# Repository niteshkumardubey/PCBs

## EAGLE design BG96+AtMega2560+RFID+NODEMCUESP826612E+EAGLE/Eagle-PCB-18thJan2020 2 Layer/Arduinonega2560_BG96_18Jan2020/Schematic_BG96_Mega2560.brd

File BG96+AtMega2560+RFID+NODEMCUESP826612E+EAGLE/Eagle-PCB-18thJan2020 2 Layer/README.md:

# Eagle-PCB
All the PCBs are designed in Autodesk Eagle

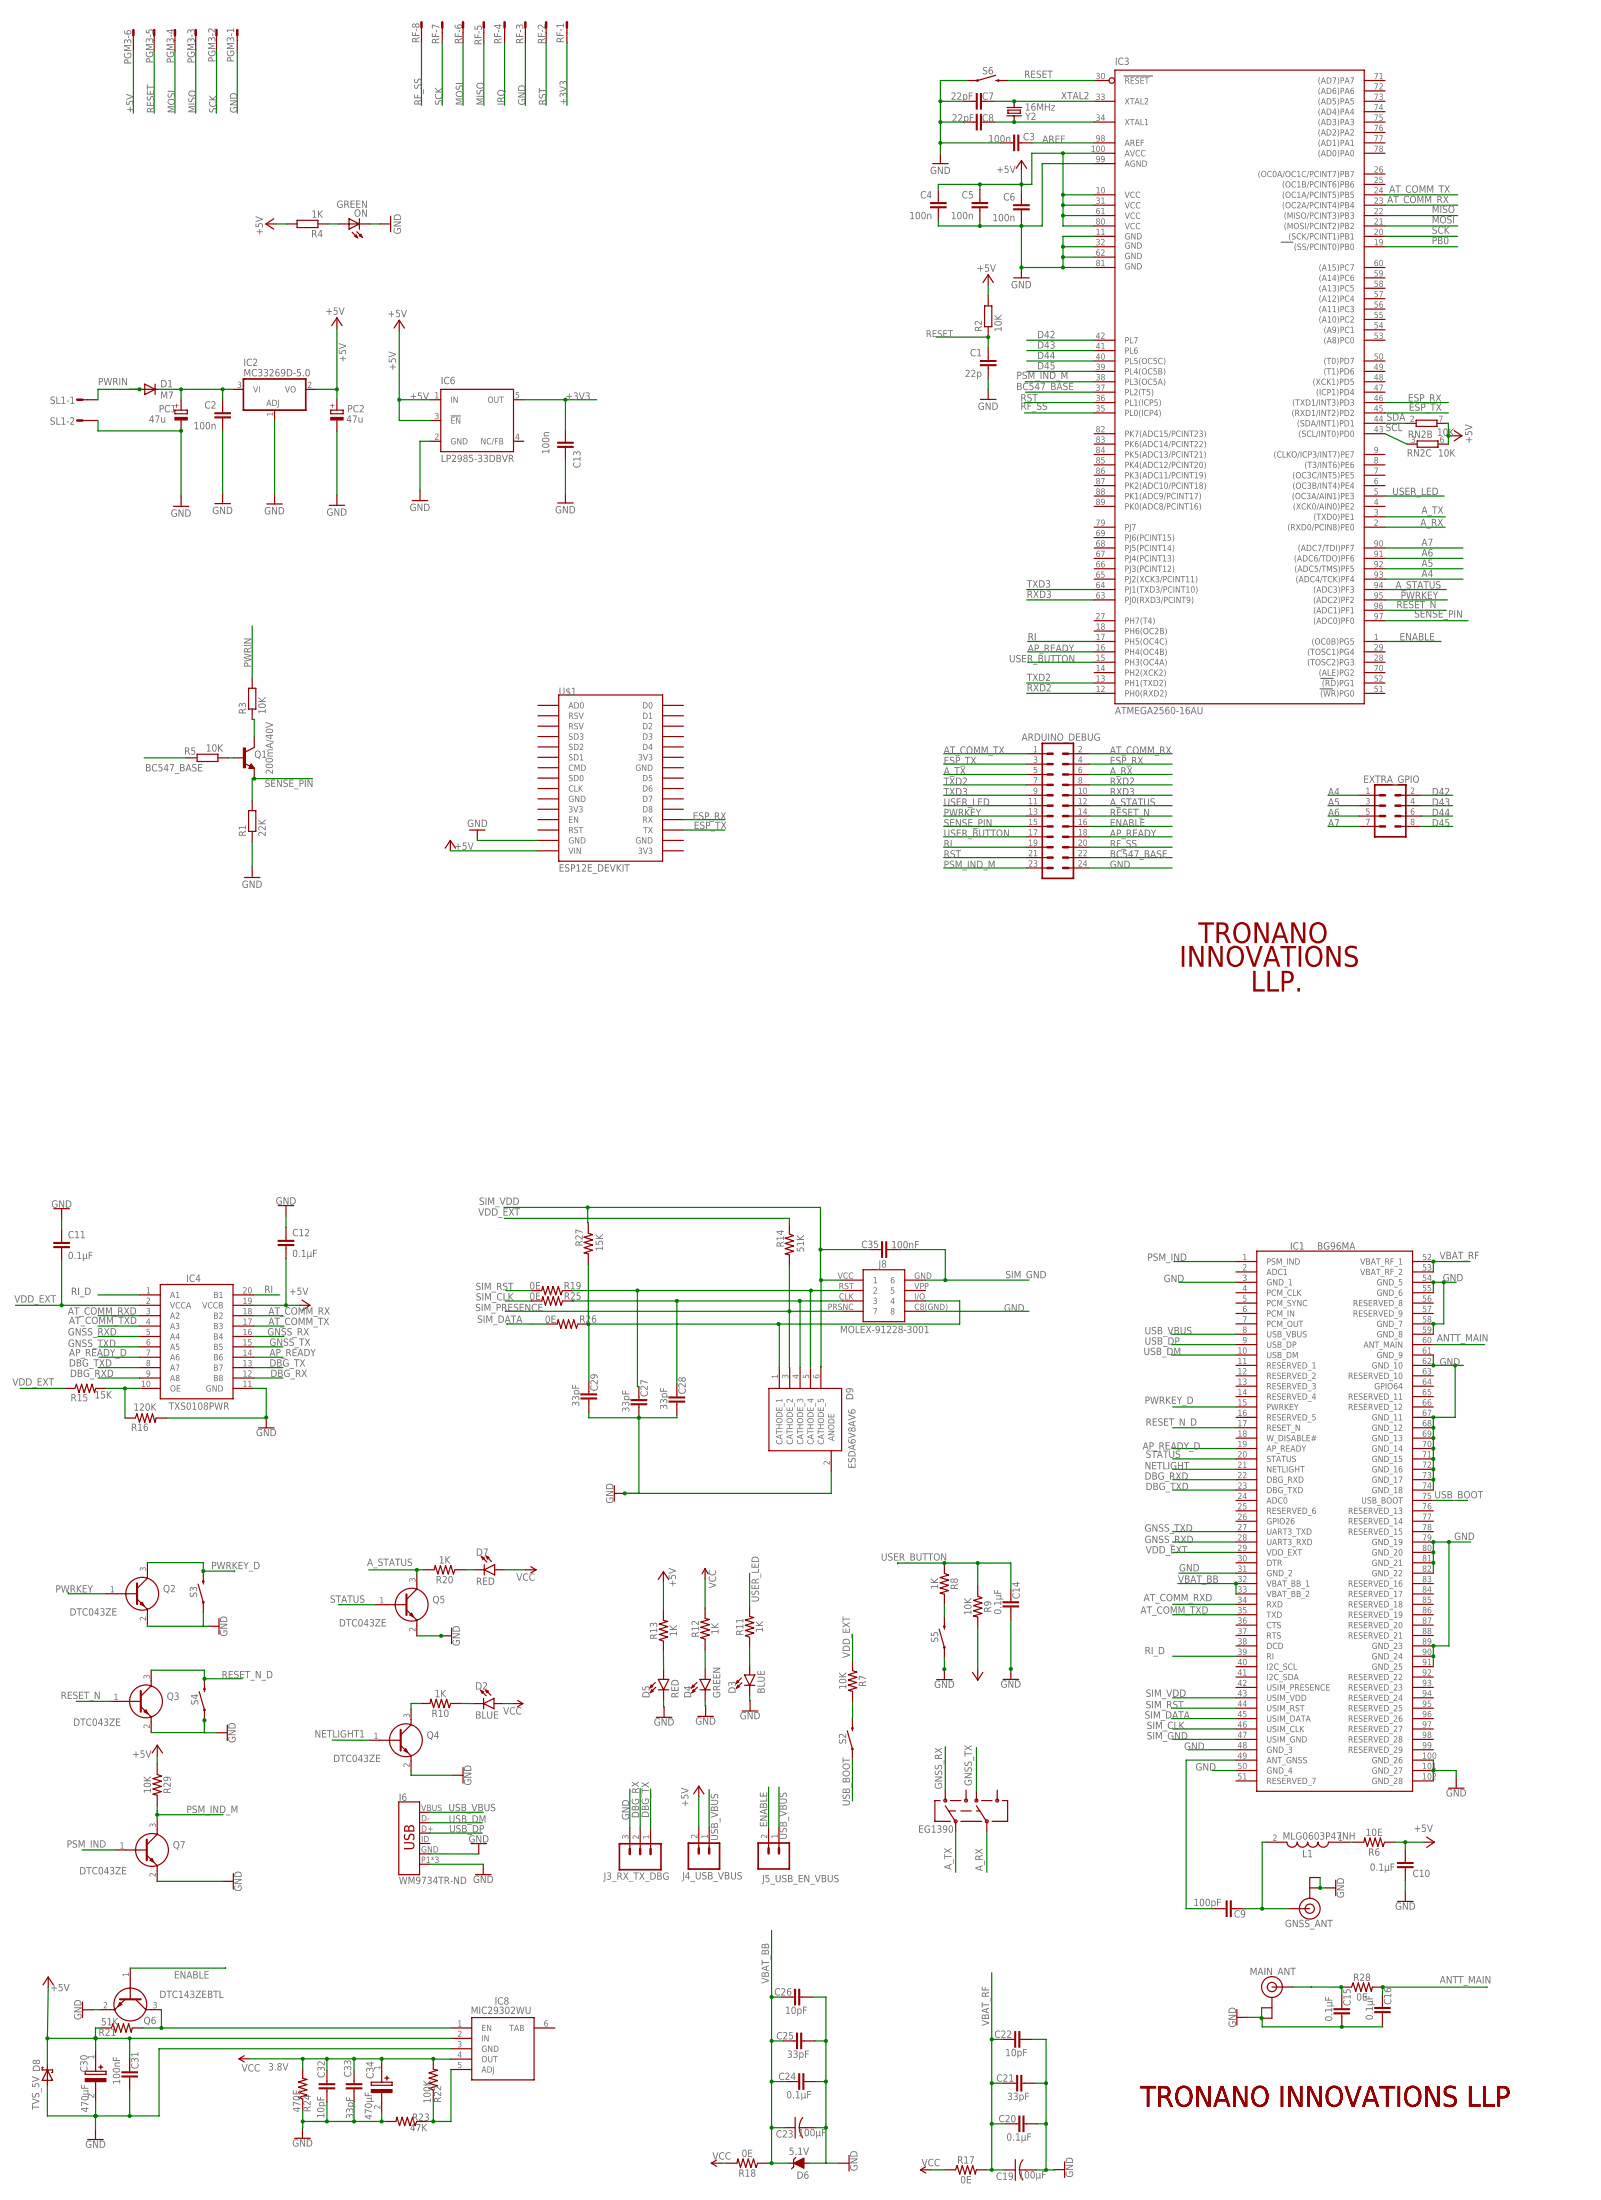
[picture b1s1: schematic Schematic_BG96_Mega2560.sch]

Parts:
ARDUINO_DEBUG: CONN_12X2; 2X12
C1: 22p; C0805
C2, C3, C4, C5, C6, C13: 100n; C0805
C7, C8: 22pF; C0805
C9: 100pF; 0805
C10, C11, C12, C14, C15, C16, C20, C24: 0.1µF; 0805
C19, C23: 100µF; C0805K
C21, C25, C27, C28, C29, C33: 33pF; 0805
C22, C26, C32: 10pF; 0805
C30, C34: 470µF; CAPPM7343X310N
C31, C35: 100nF; 0805
D1: M7; SMB
D2, D3: BLUE; LED-1206
D4: GREEN; LED-1206
D5, D7: RED; LED-1206
D6: 5.1V; SOD-323
D8: TVS_5V; SOD123FL
D9: ESDA6V8AV6; SOTFL50P160X60-6N
EG1390: SWITCH-DPDT-SMD-AYZ0202; SWITCH_DPDT_SMD_AYZ0202
EXTRA_GPIO: CONN_04X2; 2X4
GNSS_ANT: U.FL
IC1: BG96MA
IC2: MC33269D-5.0; DPACK
IC3: ATMEGA2560-16AU; TQFP100
IC4: TXS0108PWR; SOP65P640X120-20N
IC6: LP2985-33DBVR; SOT23-DBV
IC8: MIC29302WU; 6-PIN-TO-263
J3_RX_TX_DBG: CONN_03LOCK; 1X03_LOCK
J4_USB_VBUS, J5_USB_EN_VBUS: CONN_02; 1X02
J6: WM9734TR-ND; USB-B-MICRO-SMD_VERT
J8: MOLEX-91228-3001; MOLEX-912283001
L1: MLG0603P47NH; INDC0603X33N
MAIN_ANT: U.FL
ON: GREEN; CHIPLED_1206
PC1, PC2: 47u; PANASONIC_D
PGM3: S06P
Q1: 200mA/40V; TO-92-EZ
Q2, Q3, Q4, Q5, Q7: DTC043ZE; SOTFL50P160X85-3N
Q6: DTC143ZEBTL; SOTFL50P160X85-3N
R1: 22K; R0805W
R2: 10K; R0805
R3, R5: 10K; R0805W
R4: 1K; R0805
R6: 10E; 0805
R7, R9, R29: 10K; 0805
R8, R10, R11, R12, R13, R20: 1K; 0805
R14, R21: 51K; 0805
R15, R27: 15K; 0805
R16: 120K; 0805
R17, R18, R19, R25, R26, R28: 0E; 0805
R22: 100K; 0805
R23: 47K; 0805
R24: 470E; 0805
RF: S08P
RN2: 10K; CAT16
S2: USB_BOOT_SMD-6.2; TACTILE_SWITCH_SMD_6.2MM_TALL
S3: PWR_KEY_SMD-6.2; TACTILE_SWITCH_SMD_6.2MM_TALL
S4: RST_SMD-6.2; TACTILE_SWITCH_SMD_6.2MM_TALL
S5: USR_SMD-6.2; TACTILE_SWITCH_SMD_6.2MM_TALL
S6: ARD_RST; TACTILE_SWITCH_SMD_6.2MM_TALL
SL1: M02S; 02P
U$1: ESP12E_DEVKIT
Y2: 16MHz; HC49US

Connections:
3.8V: C32.1, C33.1, C34.1 (+), IC8.4 (OUT), R22.2, R24.2
+3V3: C13.2, IC6.5 (OUT), RF.1
+5V: C4.1, C5.1, C6.1, C10.1, C12.2, C30.1 (+), C31.1, D8.C, IC2.2 (VO), IC3.10 (VCC), IC3.31 (VCC1), IC3.61 (VCC2), IC3.80 (VCC3), IC3.100 (AVCC), IC4.19 (VCCB), IC6.1 (IN), IC6.3 (!EN), IC8.2 (IN), J4_USB_VBUS.2, PC2.+, PGM3.6, R2.2, R4.2, R6.1, R9.2, R13.2, R21.1, R29.1, RN2.6 (2), RN2.7 (2), U$1.VIN
A4: EXTRA_GPIO.1, IC3.93 ((ADC4/TCK)PF4)
A5: EXTRA_GPIO.3, IC3.92 ((ADC5/TMS)PF5)
A6: EXTRA_GPIO.5, IC3.91 ((ADC6/TDO)PF6)
A7: EXTRA_GPIO.7, IC3.90 ((ADC7/TDI)PF7)
ANTT_MAIN: C16.1, IC1.60 (ANT_MAIN), R28.2
AP_READY: ARDUINO_DEBUG.18, IC3.16 (PH4(OC4B)), IC4.14 (B6)
AP_READY_D: IC1.19 (AP_READY), IC4.7 (A6)
AREF: C3.1, IC3.98 (AREF)
AT_COMM_RX: ARDUINO_DEBUG.2, IC3.23 ((OC2A/PCINT4)PB4), IC4.18 (B2)
AT_COMM_RXD: IC1.34 (RXD), IC4.3 (A2)
AT_COMM_TX: ARDUINO_DEBUG.1, IC3.24 ((OC1A/PCINT5)PB5), IC4.17 (B3)
AT_COMM_TXD: IC1.35 (TXD), IC4.4 (A3)
A_RX: ARDUINO_DEBUG.6, EG1390.5, IC3.2 ((RXD0/PCIN8)PE0)
A_STATUS: ARDUINO_DEBUG.12, IC3.94 ((ADC3)PF3), Q5.3 (C), R20.2
A_TX: ARDUINO_DEBUG.5, EG1390.2, IC3.3 ((TXD0)PE1)
BC547_BASE: ARDUINO_DEBUG.22, IC3.37 (PL2(T5)), R5.2
D42: EXTRA_GPIO.2, IC3.42 (PL7)
D43: EXTRA_GPIO.4, IC3.41 (PL6)
D44: EXTRA_GPIO.6, IC3.40 (PL5(OC5C))
D45: EXTRA_GPIO.8, IC3.39 (PL4(OC5B))
DBG_RX: IC4.12 (B8), J3_RX_TX_DBG.2
DBG_RXD: IC1.22 (DBG_RXD), IC4.9 (A8)
DBG_TX: IC4.13 (B7), J3_RX_TX_DBG.1
DBG_TXD: IC1.23 (DBG_TXD), IC4.8 (A7)
ENABLE: ARDUINO_DEBUG.16, IC3.1 ((OC0B)PG5), J5_USB_EN_VBUS.2, Q6.1 (B)
ESP_RX: ARDUINO_DEBUG.4, IC3.46 ((TXD1/INT3)PD3), U$1.RX
ESP_TX: ARDUINO_DEBUG.3, IC3.45 ((RXD1/INT2)PD2), U$1.TX
GND: ARDUINO_DEBUG.24, C1.2, C2.2, C3.2, C4.2, C5.2, C6.2, C7.2, C8.2, C10.2, C11.1, C12.1, C13.1, C14.2, C15.2, C16.2, C19.2, C20.2, C21.2, C22.2, C23.2, C24.2, C25.2, C26.2, C27.2, C28.2, C29.2, C30.2 (-), C31.2, C32.2, C33.2, C34.2 (-), D3.C, D4.C, D5.C, D6.A, D8.A, D9.2 (ANODE), GNSS_ANT.1 (GND), GNSS_ANT.2 (GND), IC1.3 (GND_1), IC1.31 (GND_2), IC1.48 (GND_3), IC1.50 (GND_4), IC1.54 (GND_5), IC1.55 (GND_6), IC1.58 (GND_7), IC1.59 (GND_8), IC1.61 (GND_9), IC1.62 (GND_10), IC1.67 (GND_11), IC1.68 (GND_12), IC1.69 (GND_13), IC1.70 (GND_14), IC1.71 (GND_15), IC1.72 (GND_16), IC1.73 (GND_17), IC1.74 (GND_18), IC1.79 (GND_19), IC1.80 (GND_20), IC1.81 (GND_21), IC1.82 (GND_22), IC1.89 (GND_23), IC1.90 (GND_24), IC1.91 (GND_25), IC1.100 (GND_26), IC1.101 (GND_27), IC1.102 (GND_28), IC2.1 (ADJ), IC3.11 (GND), IC3.32 (GND1), IC3.62 (GND2), IC3.81 (GND3), IC3.99 (AGND), IC4.11 (GND), IC6.2 (GND), IC8.3 (GND), J3_RX_TX_DBG.3, J6.GND, J6.P1 (SHIELD), J6.P2 (SHIELD), J6.P3 (SHIELD), J8.C8(GND) (8), MAIN_ANT.1 (GND), MAIN_ANT.2 (GND), ON.C, PC1.-, PC2.-, PGM3.1, Q2.2 (E), Q3.2 (E), Q4.2 (E), Q5.2 (E), Q6.2 (E), Q7.2 (E), R1.1, R16.2, R23.2, R24.1, RF.3, S3.A2 (1), S4.A2 (1), S5.A2 (1), S6.A2 (1), SL1.2, U$1.GND@1 (GND)
GNSS_RX: EG1390.1, IC4.16 (B4)
GNSS_RXD: IC1.28 (UART3_RXD), IC4.5 (A4)
GNSS_TX: EG1390.4, IC4.15 (B5)
GNSS_TXD: IC1.27 (UART3_TXD), IC4.6 (A5)
IRQ: RF.4
MISO: IC3.22 ((MISO/PCINT3)PB3), PGM3.3, RF.5
MOSI: IC3.21 ((MOSI/PCINT2)PB2), PGM3.4, RF.6
unnamed: Q1.2 (B), R5.1
unnamed: Q1.3 (C), R3.1
unnamed: ON.A, R4.1
unnamed: IC8.5 (ADJ), R22.1, R23.1
unnamed: IC8.1 (EN), Q6.3 (C), R21.2
unnamed: C15.1, MAIN_ANT.FEED (SIGNAL), R28.1
unnamed: C28.1, D9.4 (CATHODE_3), J8.CLK (3), R25.1
unnamed: C29.1, D9.1 (CATHODE_1), J8.I/O (4), R26.1, R27.2
unnamed: C9.2, IC1.49 (ANT_GNSS)
unnamed: C9.1, GNSS_ANT.FEED (SIGNAL), L1.2
unnamed: C27.1, D9.5 (CATHODE_4), J8.RST (2), R19.1
unnamed: L1.1, R6.2
unnamed: IC4.10 (OE), R15.2, R16.1
unnamed: R7.2, S2.B2 (2)
unnamed: R8.2, S5.B2 (2)
unnamed: Q4.3 (C), R10.2
unnamed: D2.C, R10.1
unnamed: D3.A, R11.1
unnamed: D4.A, R12.1
unnamed: D5.A, R13.1
unnamed: D7.C, R20.1
NETLIGHT: IC1.21 (NETLIGHT)
NETLIGHT1: Q4.1 (B)
PB0: IC3.19 ((SS/PCINT0)PB0)
PSM_IND: IC1.1 (PSM_IND), Q7.1 (B)
PSM_IND_M: ARDUINO_DEBUG.23, IC3.38 (PL3(OC5A)), Q7.3 (C), R29.2
PWRIN: D1.A, R3.2, SL1.1
PWRKEY: ARDUINO_DEBUG.13, IC3.95 ((ADC2)PF2), Q2.1 (B)
PWRKEY_D: IC1.15 (PWRKEY), Q2.3 (C), S3.B2 (2)
RESET: C1.1, IC3.30 (RESET), PGM3.5, R2.1, S6.B2 (2)
RESET_N: ARDUINO_DEBUG.14, IC3.96 ((ADC1)PF1), Q3.1 (B)
RESET_N_D: IC1.17 (RESET_N), Q3.3 (C), S4.B2 (2)
RF_SS: ARDUINO_DEBUG.20, IC3.35 (PL0(ICP4)), RF.8
RI: ARDUINO_DEBUG.19, IC3.17 (PH5(OC4C)), IC4.20 (B1)
RI_D: IC1.39 (RI), IC4.1 (A1)
RST: ARDUINO_DEBUG.21, IC3.36 (PL1(ICP5)), RF.2
RXD2: ARDUINO_DEBUG.8, IC3.12 (PH0(RXD2))
RXD3: ARDUINO_DEBUG.10, IC3.63 (PJ0(RXD3/PCINT9))
SCK: IC3.20 ((SCK/PCINT1)PB1), PGM3.2, RF.7
SCL: IC3.43 ((SCL/INT0)PD0), RN2.3 (1)
SDA: IC3.44 ((SDA/INT1)PD1), RN2.2 (1)
SENSE_PIN: ARDUINO_DEBUG.15, IC3.97 ((ADC0)PF0), Q1.1 (E), R1.2
SIM_CLK: IC1.46 (USIM_CLK), R25.2
SIM_DATA: IC1.45 (USIM_DATA), R26.2
SIM_GND: C35.2, IC1.47 (USIM_GND), J8.GND (6)
SIM_PRESENCE: D9.3 (CATHODE_2), J8.PRSNC (7), R14.2
SIM_RST: IC1.44 (USIM_RST), R19.2
SIM_VDD: C35.1, D9.6 (CATHODE_5), IC1.43 (USIM_VDD), J8.VCC (1), R27.1
STATUS: IC1.20 (STATUS), Q5.1 (B)
TXD2: ARDUINO_DEBUG.7, IC3.13 (PH1(TXD2))
TXD3: ARDUINO_DEBUG.9, IC3.64 (PJ1(TXD3/PCINT10))
USB_BOOT: IC1.75 (USB_BOOT), S2.A2 (1)
USB_DM: IC1.10 (USB_DM), J6.D-
USB_DP: IC1.9 (USB_DP), J6.D+
USB_VBUS: IC1.8 (USB_VBUS), J4_USB_VBUS.1, J5_USB_EN_VBUS.1, J6.VBUS
USER_BUTTON: ARDUINO_DEBUG.17, C14.1, IC3.15 (PH3(OC4A)), R8.1, R9.1
USER_LED: ARDUINO_DEBUG.11, IC3.5 ((OC3A/AIN1)PE3), R11.2
VBAT_BB: C23.1, C24.1, C25.1, C26.1, D6.C, IC1.32 (VBAT_BB_1), IC1.33 (VBAT_BB_2), R18.1
VBAT_RF: C19.1, C20.1, C21.1, C22.1, IC1.52 (VBAT_RF_1), IC1.53 (VBAT_RF_2), R17.2
VCC: D2.A, D7.A, R12.2, R17.1, R18.2
VDD_EXT: C11.2, IC1.29 (VDD_EXT), IC4.2 (VCCA), R7.1, R14.1, R15.1
VIN1: C2.1, D1.C, IC2.3 (VI), PC1.+
XTAL1R: C8.1, IC3.34 (XTAL1), Y2.2
XTAL2: C7.1, IC3.33 (XTAL2), Y2.1

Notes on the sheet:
TRONANO
TRONANO INNOVATIONS LLP
INNOVATIONS
LLP.

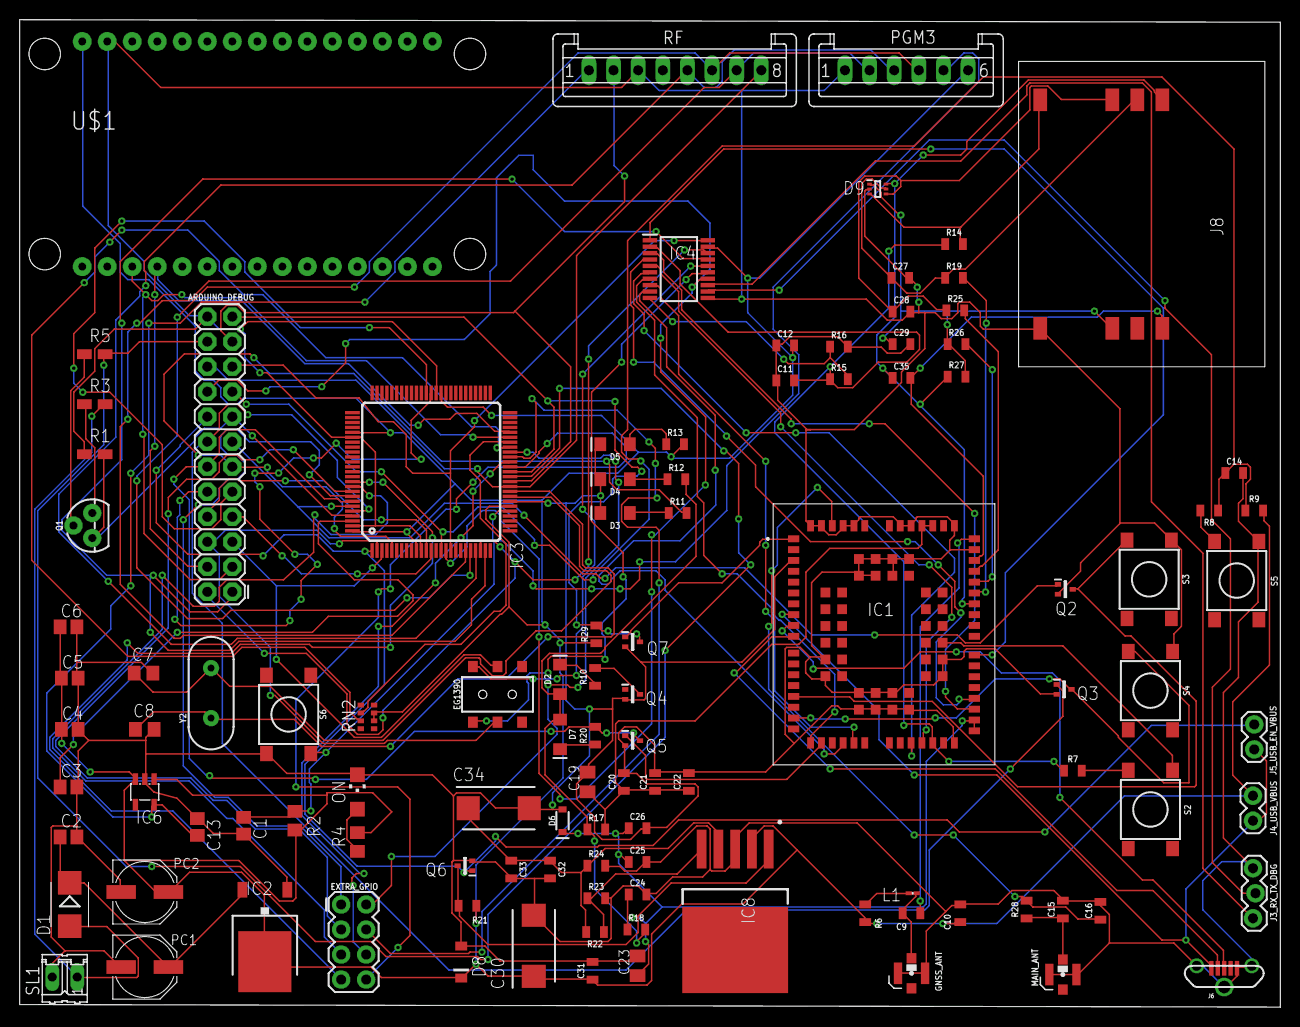
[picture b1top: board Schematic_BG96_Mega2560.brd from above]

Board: 2 copper layers, 128.0 x 100.3 mm, 109 parts (0 on the bottom side), 98 nets.

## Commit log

2020-01-30 i have changed layer spell
2020-02-03 Added BOM file which is password protected. Another BOM can be generated by schematic file.
2020-02-05 ignoring the nitesh_u file

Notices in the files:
parts and their libraries:
SparkFun-Connectors: Licensing: Creative Commons ShareAlike 4.0 International - https://creativecommons.org/licenses/by-sa/4.0
